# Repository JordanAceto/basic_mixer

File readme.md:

# Basic Eurorack 3 channel DC coupled mixer

Normal and inverting outputs are available.

Input 3 is normallized to a +5 volt reference for a convenient DC offset source.

## Status of the project:

Task | Status |
---------|--------------|
Schematic capture | &#9745;
PCB layout | &#9745;
Test build | &#9744;
Safe to order boards| &#9744;

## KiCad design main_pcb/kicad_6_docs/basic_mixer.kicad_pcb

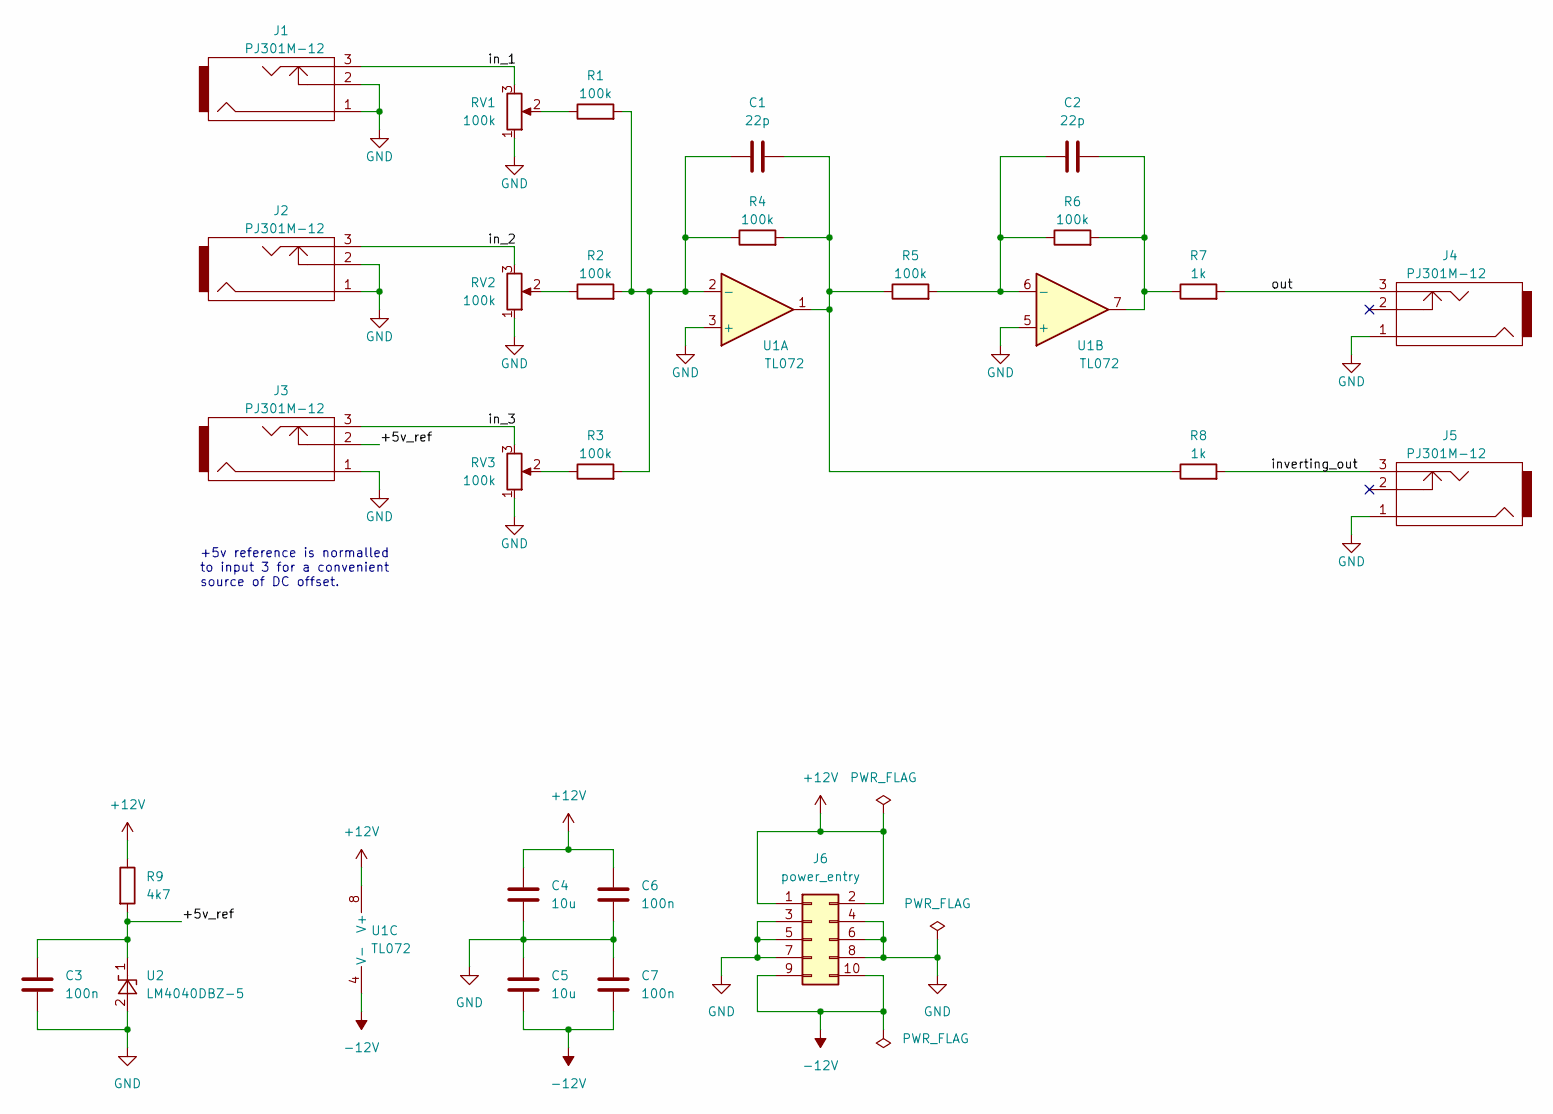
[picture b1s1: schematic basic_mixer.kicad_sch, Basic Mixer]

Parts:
C1, C2: 22p; C_0805_2012Metric
C3, C6, C7: 100n; C_0805_2012Metric
C4, C5: 10u; C_0805_2012Metric
J1, J2, J3, J4, J5: PJ301M-12
J6: power_entry; PinHeader_2x05_P2.54mm_Vertical
R1, R2, R3, R4, R5, R6: 100k; R_0805_2012Metric
R7, R8: 1k; R_0805_2012Metric
R9: 4k7; R_0805_2012Metric
RV1, RV2, RV3: 100k; Potentiometer_Alpha_RD901F-40-00D_Single_Vertical
U1: TL072; SOIC-8_3.9x4.9mm_P1.27mm
U2: LM4040DBZ-5; SOT-23

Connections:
+12V: C4.1, C6.1, J6.1, J6.2, R9.1, U1.8 (V+)
-12V: C5.2, C7.2, J6.9, J6.10, U1.4 (V-)
/+5v_ref: C3.1, J3.2, R9.2, U2.1 (K)
/in_1: J1.3, RV1.3
/in_2: J2.3, RV2.3
/in_3: J3.3, RV3.3
/inverting_out: J5.3, R8.2
/out: J4.3, R7.2
GND: C3.2, C4.2, C5.1, C6.2, C7.1, J1.1, J1.2, J2.1, J2.2, J3.1, J4.1, J5.1, J6.3, J6.4, J6.5, J6.6, J6.7, J6.8, RV1.1, RV2.1, RV3.1, U1.3 (+), U1.5 (+), U2.2 (A)
unnamed: R1.1, RV1.2
unnamed: R2.1, RV2.2
unnamed: R3.1, RV3.2
unnamed: C1.2, R4.2, R5.1, R8.1, U1.1
unnamed: C1.1, R1.2, R2.2, R3.2, R4.1, U1.2 (-)
unnamed: C2.1, R5.2, R6.1, U1.6 (-)
unnamed: C2.2, R6.2, R7.1, U1.7

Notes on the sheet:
+5v reference is normalled to input 3 for a convenient source of DC offset.

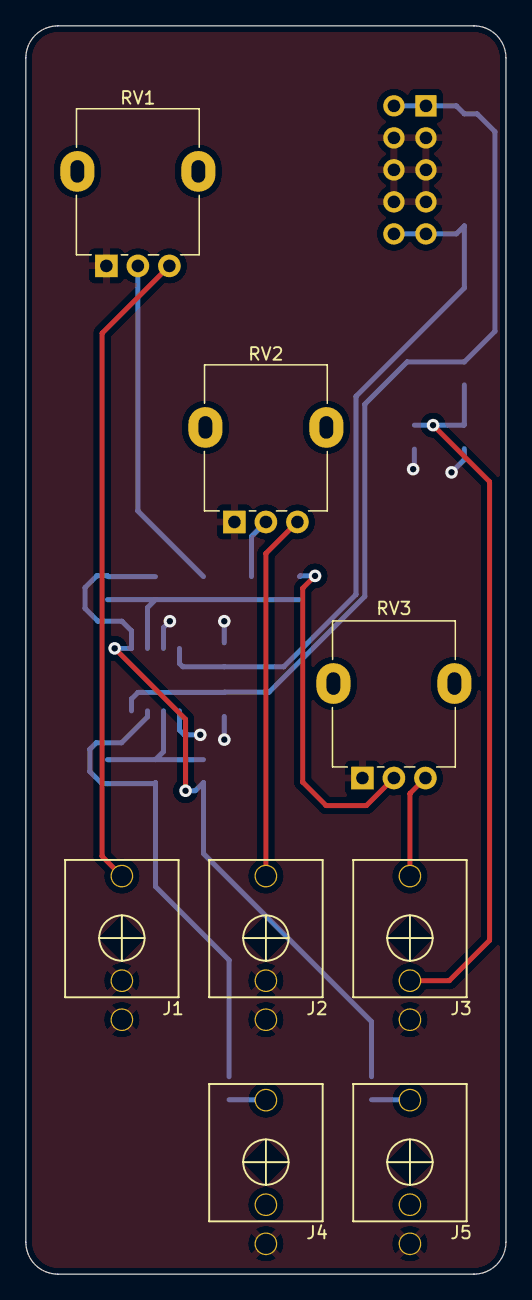
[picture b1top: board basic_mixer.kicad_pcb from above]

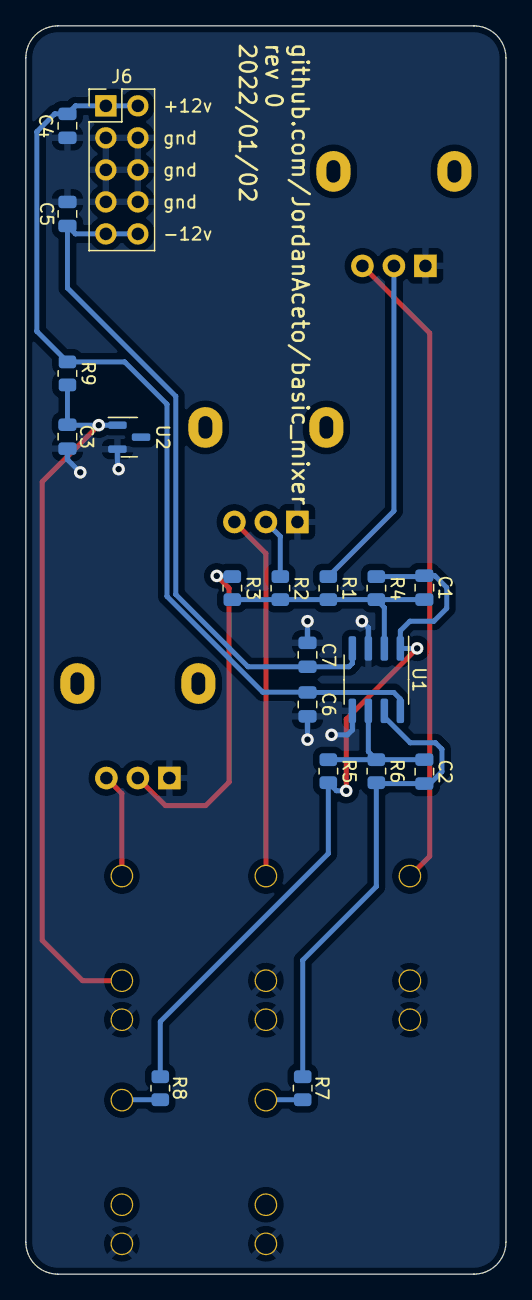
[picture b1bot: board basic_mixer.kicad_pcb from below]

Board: 2 copper layers, 38.1 x 99.1 mm, 27 parts (19 on the bottom side), 16 nets.

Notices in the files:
main_pcb/kicad_6_docs/basic_mixer.kicad_pcb:
creativecommons.org/licences/CC/by/4.0
License: CC by 4.0
main_pcb/kicad_6_docs/basic_mixer.kicad_sch:
Licence: CC by 4.0
